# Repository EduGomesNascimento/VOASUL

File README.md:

# Site VOA-SUL

Site institucional e catálogo da **VOA-SUL**, fábrica de drones FPV e recreativos
sediada em Portão (RS).

O conteúdo foi escrito a partir do *Plano Mercadológico* e do *Plano de Marketing*
da empresa: posicionamento por qualidade (e não por preço), fabricação nacional,
controladora de voo própria, homologação ANATEL e assistência técnica local.

> **Versão preliminar.** Textos, configurações de produto, preços e dados de
> contato são genéricos e servem de estrutura. Devem ser substituídos pelos dados
> reais antes da publicação.

## Estrutura

```
index.html          Página inicial: posicionamento, diferenciais, linhas e fluxo de compra
produtos.html       Catálogo das quatro linhas (FPV 5", recreativo 250 g, peças, reparo)
homologacao.html    ANATEL x ANAC, riscos do importado sem homologação, FAQ
sobre.html          A empresa, o mercado, forma de trabalho e a marca
orcamento.html      Formulário de pedido de orçamento
contato.html        Canais de atendimento
assets/
  css/style.css     Folha de estilo única (paleta da marca em variáveis CSS)
  js/main.js        Menu mobile, validação do formulário, pré-seleção de produto
  img/              Logomarca, símbolo e favicon em SVG
```

## Como rodar localmente

Não há etapa de build nem dependências. Basta abrir `index.html` no navegador,
ou servir a pasta:

```bash
python3 -m http.server 8000
# depois acesse http://localhost:8000
```

## Publicação

O site é estático e pode ser publicado no GitHub Pages direto da branch
`main` (Settings → Pages → Deploy from a branch → `main` / `/root`), ou em
qualquer hospedagem comum, apontando o domínio `voasul.com.br` para ela.

## Pontos a completar

- [ ] Fotos reais dos drones (hoje os cartões usam um marcador com o símbolo da marca)
- [ ] Especificação técnica final e preços de cada modelo
- [ ] Endereço completo, telefone/WhatsApp e horário de atendimento
- [ ] Envio do formulário de orçamento por back-end ou serviço de formulários
      (hoje o pedido é montado e aberto no cliente de e-mail do visitante)
- [ ] Fontes das estatísticas de mercado citadas em `sobre.html`

## Convenções

- HTML estático, sem framework. Cabeçalho e rodapé são repetidos em cada página.
- Toda a paleta está em variáveis CSS no topo de `assets/css/style.css`
  (`--navy`, `--sky` etc.). Mudar a cor da marca é mudar ali.
- Textos em português do Brasil.

### Animações

As animações ficam no bloco `ANIMAÇÕES`, no fim de `assets/css/style.css`.
Os blocos entram conforme a página é rolada: o `main.js` aplica a classe
`revelar` via `IntersectionObserver` — não no HTML — para que a página
continue legível se o script não carregar. Quem tem
`prefers-reduced-motion: reduce` no sistema recebe a página sem
movimento algum, com todo o conteúdo visível.

## Projeto do drone

A pasta [`drone/`](drone/README.md) guarda o quadricóptero da VoaSul: firmware (ESP32/Pico W),
placa no KiCad (caseira de face única e versão para fábrica com Gerber), frame impresso em 3D,
plano de montagem e a luva de gestos. Ela é independente do site.

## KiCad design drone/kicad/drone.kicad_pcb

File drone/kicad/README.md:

# Placa do drone no KiCad (face única, trilhas grossas)

Projeto KiCad 7 da placa redonda (Ø97 mm) do drone. Abre no KiCad 7, 8 ou 9.

| Arquivo | O que é |
|---|---|
| `drone.kicad_pro` / `.kicad_sch` / `.kicad_pcb` | o projeto: esquema e placa |
| `drone.kicad_dru` | regras extras (sensores e resistores embaixo do ESP32 de propósito) |
| `projeto.py` | **a fonte de tudo**: peças, redes, posições, larguras e pinos do ESP32 |
| `gerar.py`, `etapas.py` | montam a placa a partir do `projeto.py` (Python do KiCad) |
| `rotear.py` | roteador próprio para face única (só numpy) |
| `gerar_esquema.py` | gera o esquema a partir do `projeto.py` |
| `modelos3d.py` + `3d/` | modelos 3D (ESP32 DevKit, MT3608, GY-BMI160, GY-BMP280 feitos aqui; o resto da biblioteca do KiCad) |
| `saidas/` | PDFs de transferência, imagens 3D, lista de redes, relatório de DRC |

## Regras da placa

- **Face única:** todo o cobre fica embaixo (B.Cu). Onde duas trilhas teriam de se cruzar
  entra um **jumper**: fio rígido por cima, do lado dos componentes (aparece como trilha fina em F.Cu
  entre duas vias, e desenhado na folha de montagem).
- **Trilhas grossas:** 2,5 mm (VBAT, drenos dos motores) · 1,5 mm (GND, 5 V, 3V3) · 1,2 mm (sinais).
  Só afinam para 0,8 mm nos últimos 3 mm antes de um pino de passo 2,54.
- **Folga de 0,8 mm** entre cobres de redes diferentes, inclusive entre ilhas de pinos (ilhas
  ovais de 1,7 × 3,0 mm), para o toner amassado não encostar.
- **Anel de VBAT** de 2,5 mm por dentro da borda, e **plano de GND** no resto.
- Peças SMD (MOSFET SOT-23, diodo SS34, capacitor 0805) ficam **embaixo, no lado do cobre**,
  fora dos raios do frame (que passam a 2 mm da placa nas diagonais).
- **BMI160 e BMP280 ficam embaixo do ESP32**, entre as barras fêmea (8,5 mm de vão), soldados
  direto com barra macho. O giroscópio fica perto do centro do drone.

## Pinos do ESP32 (mudaram!)

Para não cruzar trilha, os pinos seguem a ordem física dos braços. O `include/board_esp32.h`
já está atualizado:

| Função | GPIO | | Função | GPIO |
|---|---|---|---|---|
| Motor FR | 17 | | Sonar baixo TRIG / ECHO | 14 / 27 |
| Motor RR | 4 | | Sonar frente TRIG / ECHO | 13 / 12 |
| Motor RL | 23 | | IR esquerdo / direito | 36 / 39 |
| Motor FL | 19 | | Bateria (ADC1) | 35 |
| I²C 1 (BMP280) SDA / SCL | 21 / 22 | | LED | 2 |
| I²C 2 (BMI160) SDA / SCL | 16 / 18 | | Fluxo óptico MISO / SCK / MOSI / CS | 32 / 33 / 25 / 26 |

## Fluxo óptico (J4): opcional

O **J4** é o conector do sensor de fluxo óptico **PMW3901** (SPI). A placa e o firmware
funcionam **com e sem** o módulo:

- sem o módulo, o J4 fica vazio e o drone voa como sempre;
- com o módulo, o firmware o encontra sozinho no boot (lê o ID do chip) e passa a frear a
  deriva quando o manche está solto. A página do celular mostra o estado no quadro **Fluxo**;
- se o módulo parar de responder em voo (fio solto), o firmware percebe em menos de 1 s e
  segue sem ele.

O J4 é uma barra **2×3** logo abaixo do ESP32. Visto de cima: fileira de cima **MISO, SCK, MOSI**;
fileira de baixo **3V3, GND, CS** (o quadrado verde da folha de montagem é o 3V3).
O módulo vai embaixo do drone, com a lente para baixo. Ligue e desligue só com o drone
**desligado**. Teste e ajuste: `docs/PLANO_DE_MONTAGEM.md`, fase 12.

## Arquivos para usar já

| Para | Arquivo |
|---|---|
| Transferência térmica (imprimir 1:1, laser) | `saidas/transferencia_B_Cu.pdf` |
| Montagem por cima / por baixo | `saidas/montagem_cima.pdf`, `saidas/montagem_baixo_vista_por_baixo.pdf` |
| Lista de jumpers | `saidas/jumpers.txt` (11: 6 de GND, 1 de 3V3, 4 de sinal de motor) |
| Teste de continuidade | `saidas/redes.txt` |
| Esquema | `saidas/esquema.pdf` |
| Mandar fazer na fábrica | `pro/drone_pro_gerber.zip` (+ `pro/drone_pro.kicad_pcb`) |
| Ver em 3D | `saidas/drone3d_*.png`; interativo: `python3 -m http.server` nesta pasta e abrir `saidas/visualizador3d.html` |

## Regerar tudo

Tudo de uma vez: `./gerar_tudo.sh` (leva uns 30–40 minutos por causa do roteador). Passo a passo:

```bash
python3 gerar.py placa        # peças e redes (Python do KiCad: /usr/bin/python3)
python3 gerar.py exportar     # geometria.json para o roteador
python3 rotear.py geometria.json rotas.json   # qualquer Python com numpy
python3 gerar.py aplicar      # trilhas, jumpers, plano de GND
python3 gerar.py drc          # verificação de regras -> drc.txt
python3 gerar_esquema.py      # esquema
python3 gerar.py saidas       # PDFs de transferência e 3D
```

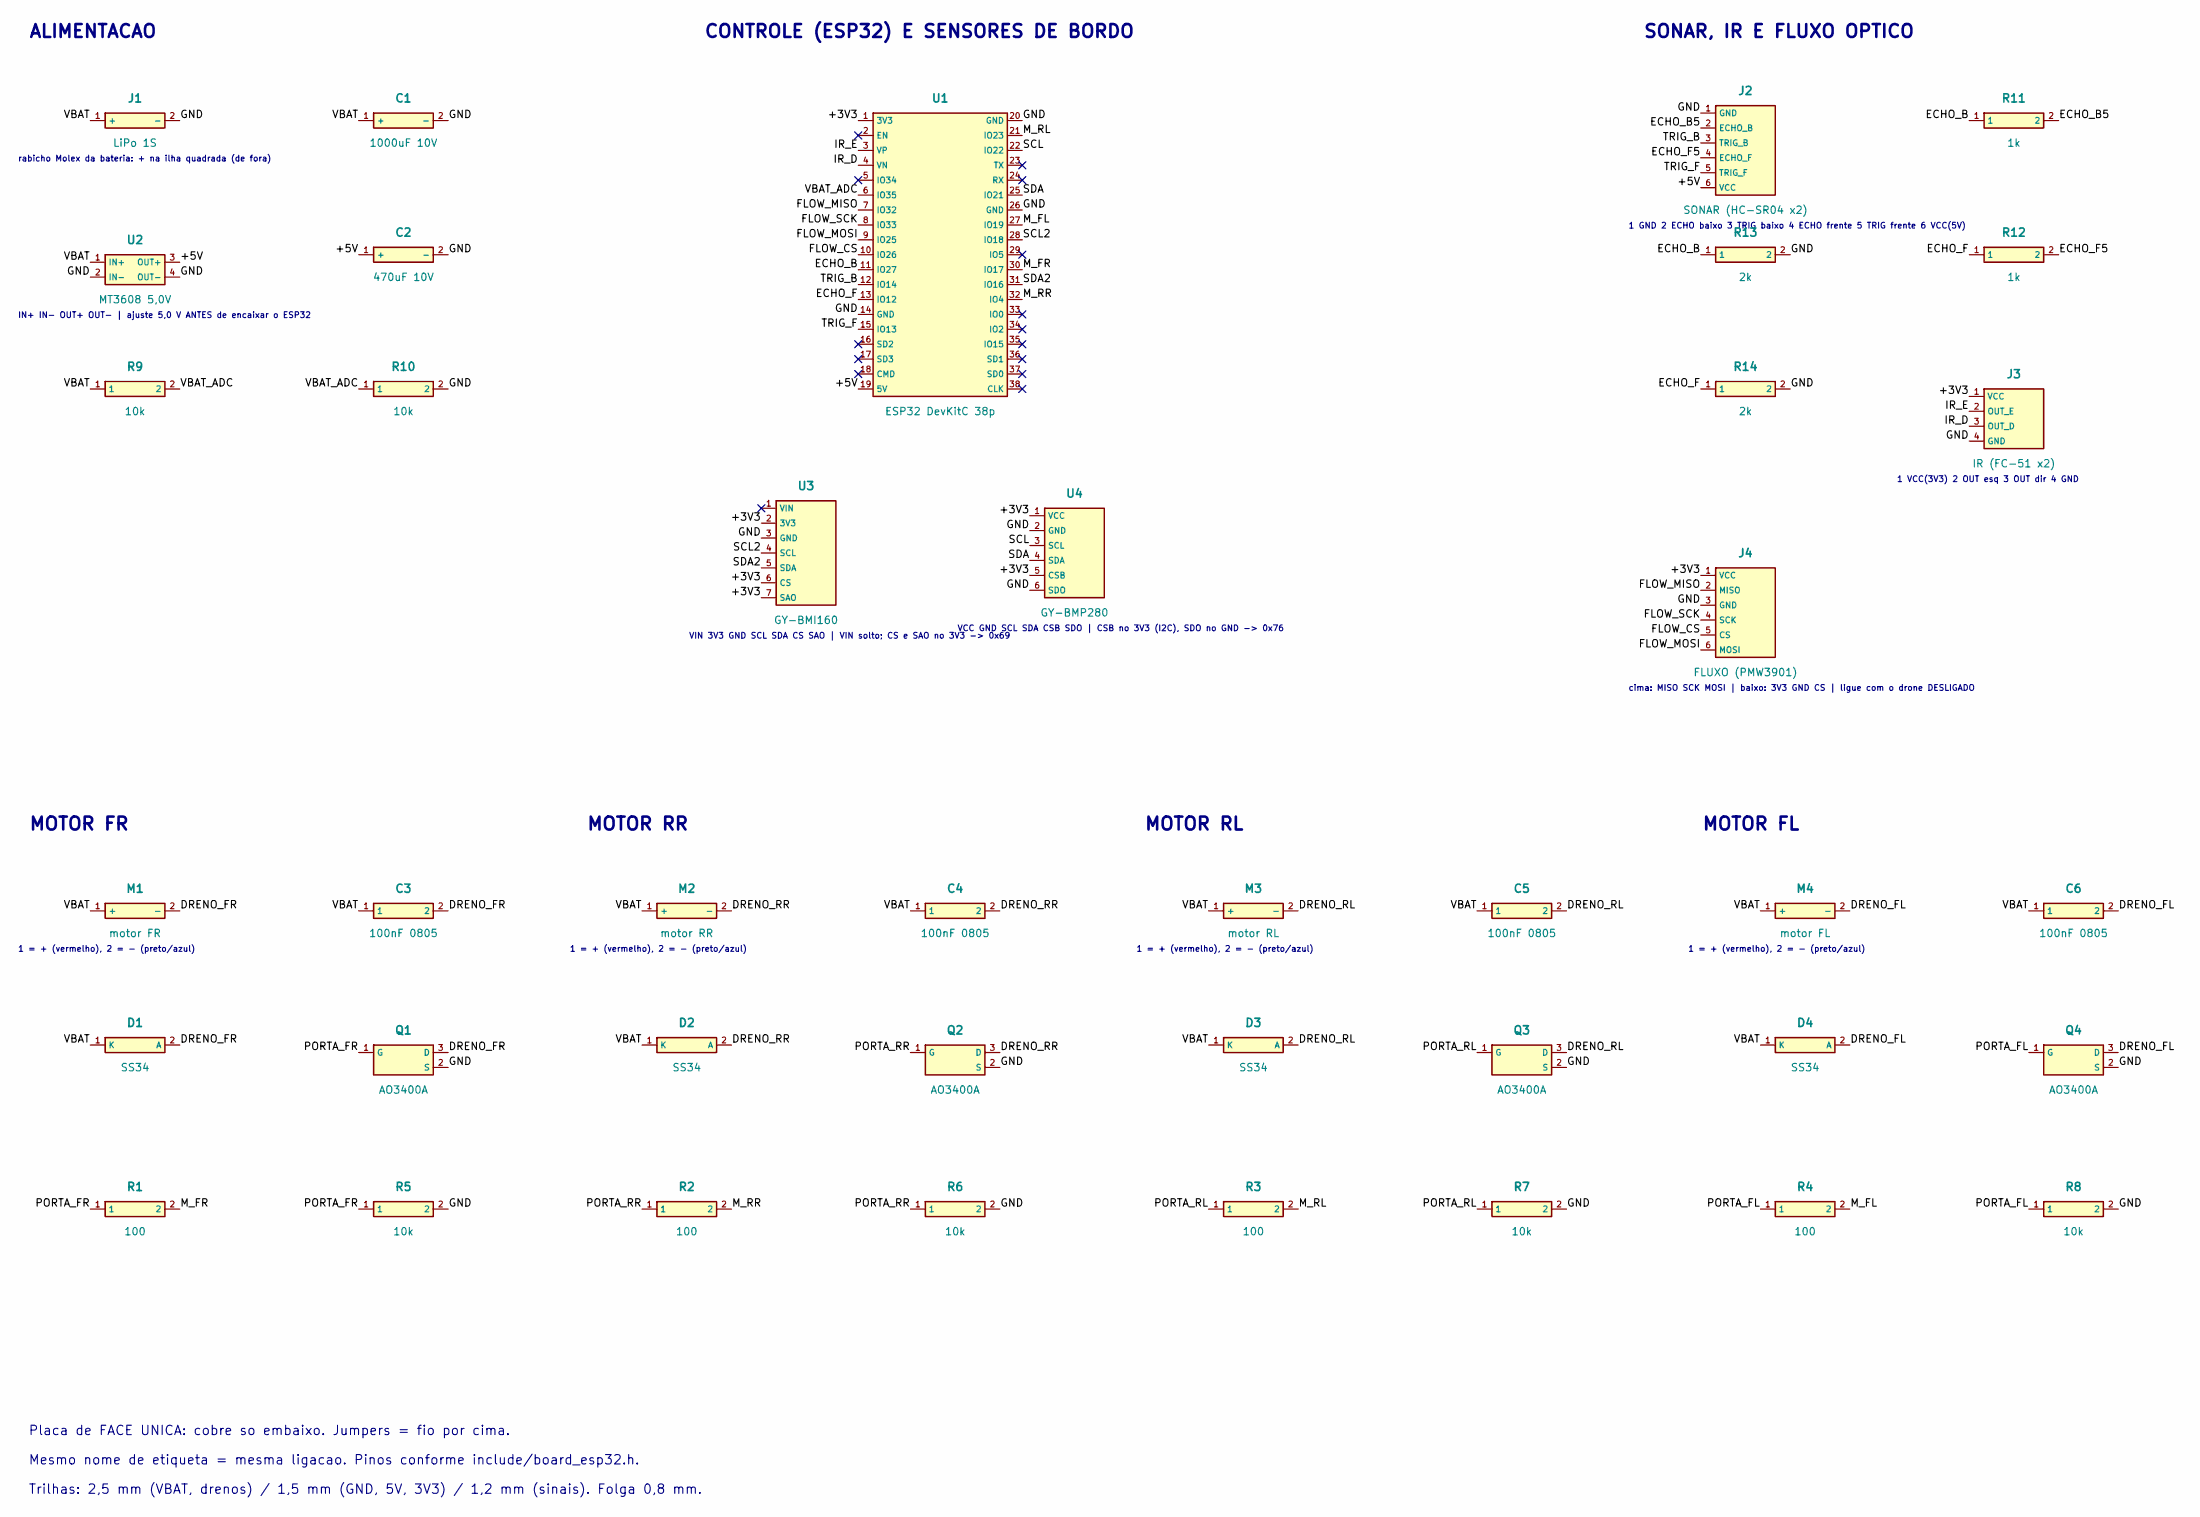
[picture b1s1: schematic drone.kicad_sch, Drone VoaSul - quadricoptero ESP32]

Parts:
C1: 1000uF 10V; CP_Radial_D8.0mm_P3.50mm
C2: 470uF 10V; CP_Radial_D6.3mm_P2.50mm
C3, C4, C5, C6: 100nF 0805; C_0805_2012Metric
D1, D2, D3, D4: SS34; D_SMA
J1: LiPo 1S; Ilhas_bateria
J2: SONAR (HC-SR04 x2); PinHeader_1x06_P2.54mm_Vertical
J3: IR (FC-51 x2); PinHeader_1x04_P2.54mm_Vertical
J4: FLUXO (PMW3901); PinHeader_2x03_P2.54mm_Vertical
M1: motor FR; Ilhas_motor
M2: motor RR; Ilhas_motor
M3: motor RL; Ilhas_motor
M4: motor FL; Ilhas_motor
Q1, Q2, Q3, Q4: AO3400A; SOT-23
R1, R2, R3, R4: 100; R_Axial_DIN0204_L3.6mm_D1.6mm_P2.54mm_Vertical
R5, R6, R7, R8, R9, R10: 10k; R_Axial_DIN0204_L3.6mm_D1.6mm_P2.54mm_Vertical
R11, R12: 1k; R_Axial_DIN0204_L3.6mm_D1.6mm_P2.54mm_Vertical
R13, R14: 2k; R_Axial_DIN0204_L3.6mm_D1.6mm_P2.54mm_Vertical
U1: ESP32 DevKitC 38p; ESP32_DevKitC_38p
U2: MT3608 5,0V; MT3608_modulo
U3: GY-BMI160; GY_BMI160
U4: GY-BMP280; GY_BMP280

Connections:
+3V3: J3.1 (VCC), J4.1 (VCC), U1.1 (3V3), U3.2 (3V3), U3.6 (CS), U3.7 (SAO), U4.1 (VCC), U4.5 (CSB)
+5V: C2.1 (+), J2.6 (VCC), U1.19 (5V), U2.3 (OUT+)
DRENO_FL: C6.2, D4.2 (A), M4.2 (-), Q4.3 (D)
DRENO_FR: C3.2, D1.2 (A), M1.2 (-), Q1.3 (D)
DRENO_RL: C5.2, D3.2 (A), M3.2 (-), Q3.3 (D)
DRENO_RR: C4.2, D2.2 (A), M2.2 (-), Q2.3 (D)
ECHO_B: R11.1, R13.1, U1.11 (IO27)
ECHO_B5: J2.2 (ECHO_B), R11.2
ECHO_F: R12.1, R14.1, U1.13 (IO12)
ECHO_F5: J2.4 (ECHO_F), R12.2
FLOW_CS: J4.5 (CS), U1.10 (IO26)
FLOW_MISO: J4.2 (MISO), U1.7 (IO32)
FLOW_MOSI: J4.6 (MOSI), U1.9 (IO25)
FLOW_SCK: J4.4 (SCK), U1.8 (IO33)
GND: C1.2 (-), C2.2 (-), J1.2 (-), J2.1 (GND), J3.4 (GND), J4.3 (GND), Q1.2 (S), Q2.2 (S), Q3.2 (S), Q4.2 (S), R5.2, R6.2, R7.2, R8.2, R10.2, R13.2, R14.2, U1.14 (GND), U1.20 (GND), U1.26 (GND), U2.2 (IN-), U2.4 (OUT-), U3.3 (GND), U4.2 (GND), U4.6 (SDO)
IR_D: J3.3 (OUT_D), U1.4 (VN)
IR_E: J3.2 (OUT_E), U1.3 (VP)
M_FL: R4.2, U1.27 (IO19)
M_FR: R1.2, U1.30 (IO17)
M_RL: R3.2, U1.21 (IO23)
M_RR: R2.2, U1.32 (IO4)
PORTA_FL: Q4.1 (G), R4.1, R8.1
PORTA_FR: Q1.1 (G), R1.1, R5.1
PORTA_RL: Q3.1 (G), R3.1, R7.1
PORTA_RR: Q2.1 (G), R2.1, R6.1
SCL: U1.22 (IO22), U4.3 (SCL)
SCL2: U1.28 (IO18), U3.4 (SCL)
SDA: U1.25 (IO21), U4.4 (SDA)
SDA2: U1.31 (IO16), U3.5 (SDA)
TRIG_B: J2.3 (TRIG_B), U1.12 (IO14)
TRIG_F: J2.5 (TRIG_F), U1.15 (IO13)
VBAT: C1.1 (+), C3.1, C4.1, C5.1, C6.1, D1.1 (K), D2.1 (K), D3.1 (K), D4.1 (K), J1.1 (+), M1.1 (+), M2.1 (+), M3.1 (+), M4.1 (+), R9.1, U2.1 (IN+)
VBAT_ADC: R9.2, R10.1, U1.6 (IO35)

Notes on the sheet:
ALIMENTACAO
rabicho Molex da bateria: + na ilha quadrada (de fora)
IN+ IN- OUT+ OUT- | ajuste 5,0 V ANTES de encaixar o ESP32
CONTROLE (ESP32) E SENSORES DE BORDO
VIN 3V3 GND SCL SDA CS SAO | VIN solto; CS e SAO no 3V3 -> 0x69
VCC GND SCL SDA CSB SDO | CSB no 3V3 (I2C), SDO no GND -> 0x76
SONAR, IR E FLUXO OPTICO
1 GND 2 ECHO baixo 3 TRIG baixo 4 ECHO frente 5 TRIG frente 6 VCC(5V)
1 VCC(3V3) 2 OUT esq 3 OUT dir 4 GND
cima: MISO SCK MOSI | baixo: 3V3 GND CS | ligue com o drone DESLIGADO
MOTOR FR
1 = + (vermelho), 2 = - (preto/azul)
MOTOR RR
MOTOR RL
MOTOR FL
Placa de FACE UNICA: cobre so embaixo. Jumpers = fio por cima.
Mesmo nome de etiqueta = mesma ligacao. Pinos conforme include/board_esp32.h.
Trilhas: 2,5 mm (VBAT, drenos) / 1,5 mm (GND, 5V, 3V3) / 1,2 mm (sinais). Folga 0,8 mm.

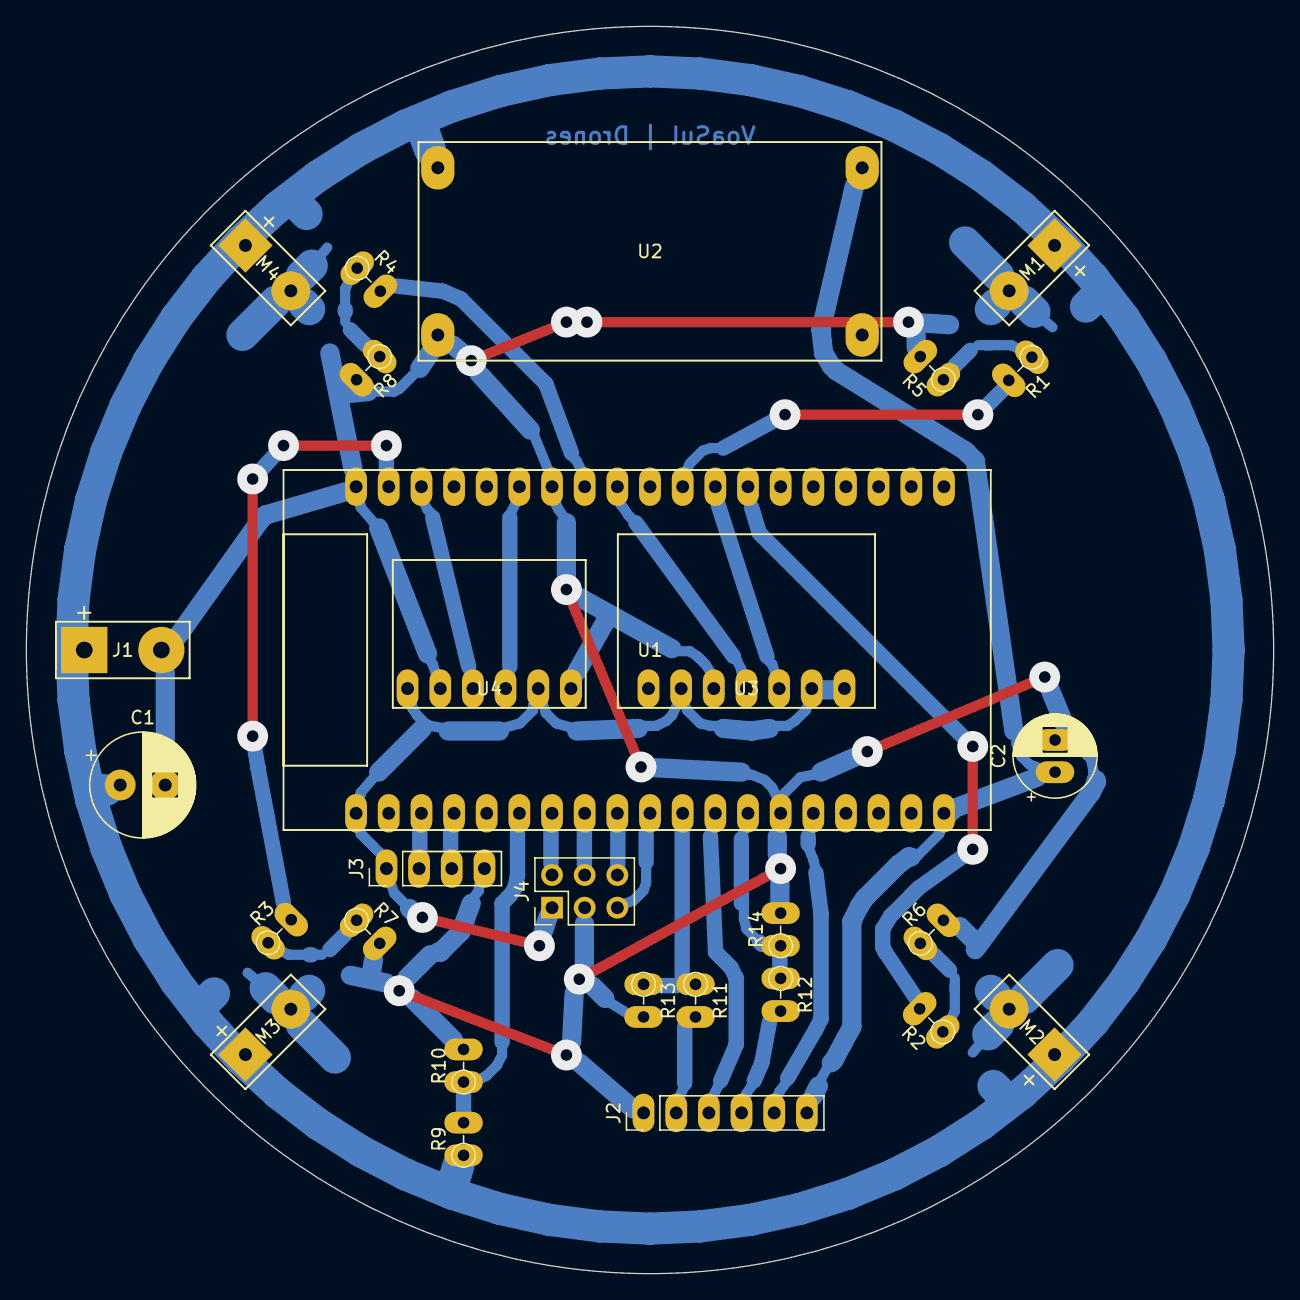
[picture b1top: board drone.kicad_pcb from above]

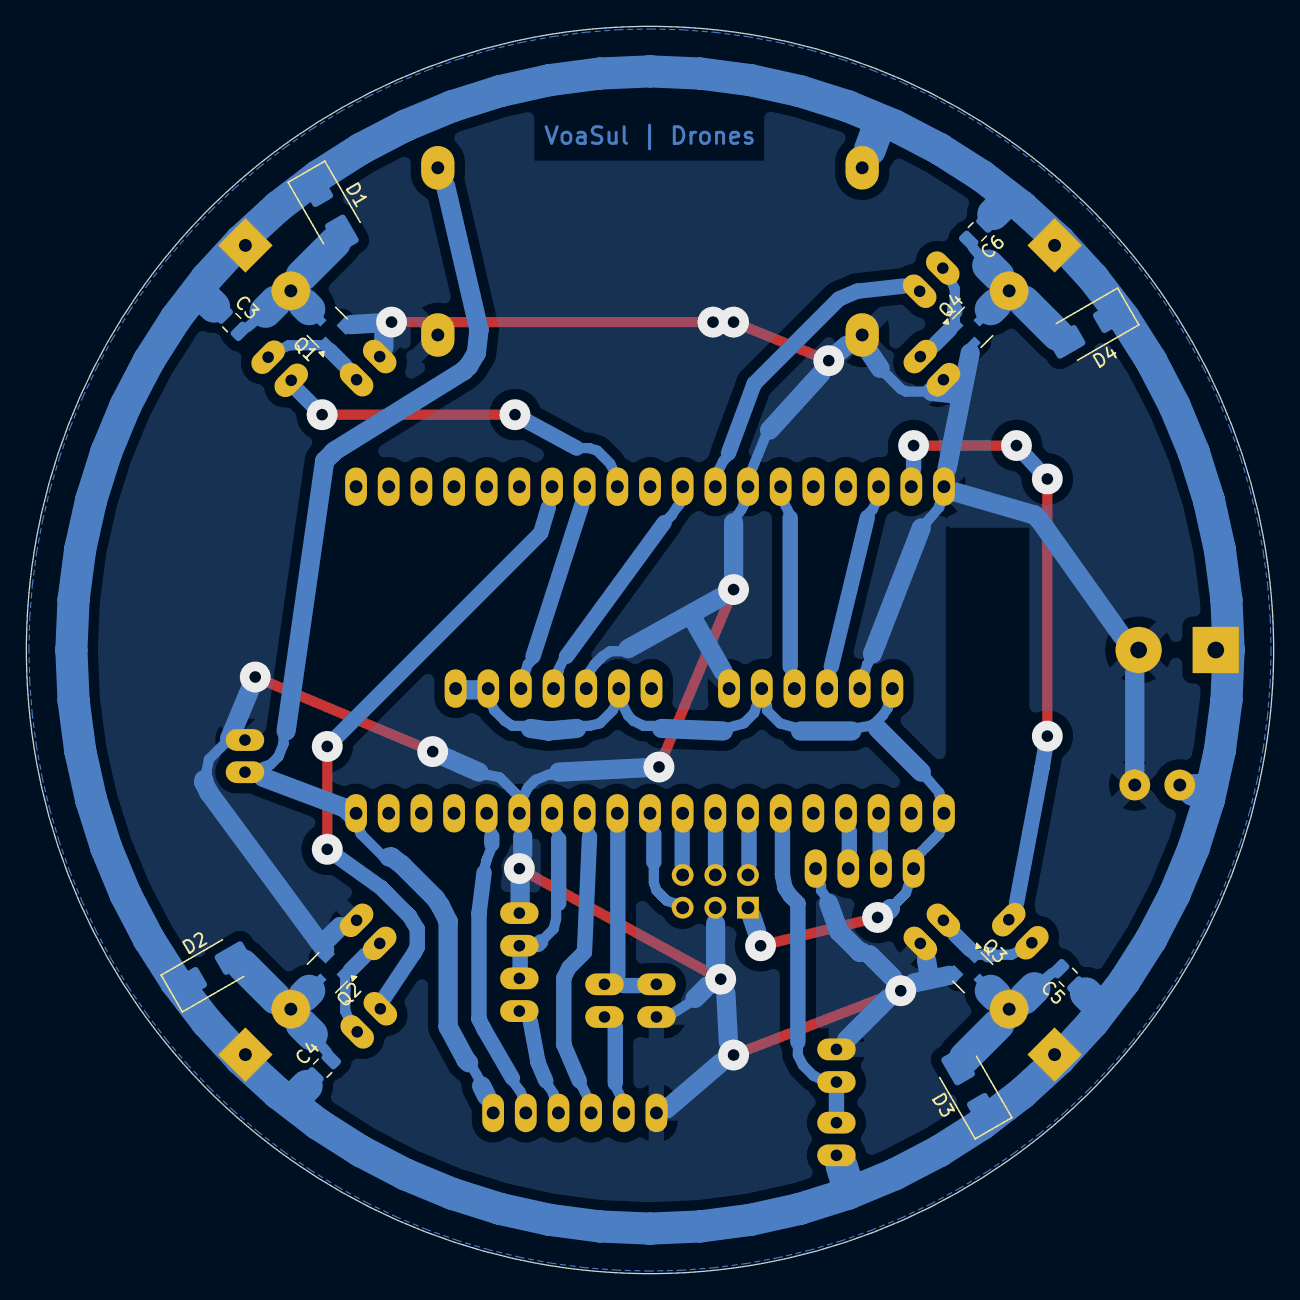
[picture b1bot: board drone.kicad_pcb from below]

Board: 2 copper layers, 97.0 x 97.0 mm, 40 parts (12 on the bottom side), 33 nets.

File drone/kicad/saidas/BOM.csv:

Qtd,Referencias,Valor,Descricao,Pegada,Montagem,Lado,LCSC,Observacao
1,C1,1000uF 10V,"Capacitor eletrolitico 1000 uF 10-16 V, D8 mm, passo 3,5 mm",CP_Radial_D8.0mm_P3.50mm,THT,cima,,polaridade
1,C2,470uF 10V,"Capacitor eletrolitico 470 uF 10-16 V, D6,3 mm, passo 2,5 mm",CP_Radial_D6.3mm_P2.50mm,THT,cima,,polaridade
4,C3 C4 C5 C6,100nF 0805,"Capacitor ceramico 100 nF 50 V X7R, 0805",C_0805_2012Metric,SMD,baixo,C49678,face de baixo
4,D1 D2 D3 D4,SS34,"Diodo Schottky SS34 40 V 3 A, SMA",D_SMA,SMD,baixo,C8678,"face de baixo, faixa para fora"
1,J1,LiPo 1S,Rabicho Molex 51005 macho com fio 24 AWG,Ilhas_bateria,THT,cima,,+ (vermelho) na ilha quadrada
1,J2,SONAR (HC-SR04 x2),"Barra de pinos macho 1x6, 2,54 mm",PinHeader_1x06_P2.54mm_Vertical,THT,cima,,conector dos sonares
1,J3,IR (FC-51 x2),"Barra de pinos macho 1x4, 2,54 mm",PinHeader_1x04_P2.54mm_Vertical,THT,cima,,conector dos IR
1,J4,FLUXO (PMW3901),"Barra de pinos macho 2x3, 2,54 mm",PinHeader_2x03_P2.54mm_Vertical,THT,cima,,fluxo optico (opcional); ou 2 pedacos de 1x3
1,M1,motor FR,Ilhas para o motor coreless 1020,Ilhas_motor,THT,cima,,fios do motor; + na ilha quadrada
1,M2,motor RR,Ilhas para o motor coreless 1020,Ilhas_motor,THT,cima,,fios do motor; + na ilha quadrada
1,M3,motor RL,Ilhas para o motor coreless 1020,Ilhas_motor,THT,cima,,fios do motor; + na ilha quadrada
1,M4,motor FL,Ilhas para o motor coreless 1020,Ilhas_motor,THT,cima,,fios do motor; + na ilha quadrada
4,Q1 Q2 Q3 Q4,AO3400A,"MOSFET canal N AO3400A 30 V 5,7 A, SOT-23",SOT-23,SMD,baixo,C20917,face de baixo
4,R1 R2 R3 R4,100,Resistor 100 ohm 1/4 W,R_Axial_DIN0204_L3.6mm_D1.6mm_P2.54mm_Vertical,THT,cima,,em pe; 100-220 ohm servem
6,R5 R6 R7 R8 R9 R10,10k,Resistor 10 kohm 1/4 W,R_Axial_DIN0204_L3.6mm_D1.6mm_P2.54mm_Vertical,THT,cima,,em pe
2,R11 R12,1k,Resistor 1 kohm 1/4 W,R_Axial_DIN0204_L3.6mm_D1.6mm_P2.54mm_Vertical,THT,cima,,em pe
2,R13 R14,2k,Resistor 2 kohm 1/4 W,R_Axial_DIN0204_L3.6mm_D1.6mm_P2.54mm_Vertical,THT,cima,,em pe; 1k8 ou 2k2 servem
1,U1,ESP32 DevKitC 38p,"Placa ESP32 DevKitC V4, 38 pinos, WROOM-32",ESP32_DevKitC_38p,THT,cima,,em 2 barras femea 1x19
1,U2,"MT3608 5,0V",Modulo step-up MT3608,MT3608_modulo,THT,cima,,"em 4 pernas de fio; ajuste 5,0 V antes do ESP32"
1,U3,GY-BMI160,Modulo giroscopio/acelerometro GY-BMI160,GY_BMI160,THT,cima,,"barra macho baixa, embaixo do ESP32"
1,U4,GY-BMP280,Modulo barometro GY-BMP280-3.3 (6 pinos),GY_BMP280,THT,cima,,"barra macho baixa, embaixo do ESP32"
2,U1 (ESP32),,"Barra de pinos femea 1x19, 2,54 mm",,fora da placa,,,corte de 2 barras 1x40
4,M1-M4,,Motor coreless 1020 (2 CW + 2 CCW),,fora da placa,,,ja comprado
1,J1,,Bateria LiPo 1S 500-600 mAh 25C+ com Molex 51005,,fora da placa,,,ex.: Leao LB530LP1

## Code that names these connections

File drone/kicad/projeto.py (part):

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    'PIN_SONAR_DOWN_TRIG': 14, 'PIN_SONAR_DOWN_ECHO': 27,
    'PIN_SONAR_FRONT_TRIG': 13, 'PIN_SONAR_FRONT_ECHO': 12,
    'PIN_IR_LEFT': 36, 'PIN_IR_RIGHT': 39, 'PIN_VBAT': 35, 'PIN_STATUS_LED': 2,
    'PIN_FLOW_MISO': 32, 'PIN_FLOW_SCK': 33, 'PIN_FLOW_MOSI': 25, 'PIN_FLOW_CS': 26,
}


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# de cima (visto de cima), da esquerda p/ a direita: J3 (IR) | divisor da bateria |
# J4 (fluxo optico) | sonar (resistores + J2)
peca('J3', 'IR (FC-51 x2)', 'CONN4', -20.5, -17.0, rot=90,
     pinos={'1': '+3V3', '2': 'IR_E', '3': 'IR_D', '4': 'GND'},
     nota='1 VCC(3V3) 2 OUT esq 3 OUT dir 4 GND')
# divisor da bateria (IO34): 10k/10k, em pe
# (encostado no anel de VBAT: so o sinal fino VBAT_ADC atravessa a placa)
peca('R9', '10k', 'R_PE', -14.5, -39.3, rot=90, pinos={'1': 'VBAT', '2': 'VBAT_ADC'})
peca('R10', '10k', 'R_PE', -14.5, -33.6, rot=90, pinos={'1': 'VBAT_ADC', '2': 'GND'})
# fluxo optico PMW3901: OPCIONAL. Sem o modulo o drone voa igual; o firmware
# descobre sozinho no boot se ele esta ligado (le o ID do chip).
# Barra 2x3 logo abaixo dos pinos 32/33/25/26 do ESP32: as trilhas ficam curtinhas
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#   fileira de cima : MISO SCK MOSI   (pinos 2 4 6)
#   fileira de baixo: 3V3  GND CS     (pinos 1 3 5)
peca('J4', 'FLUXO (PMW3901)', 'CONN2x3', -7.62, -20.04, rot=90,
     pinos={'1': '+3V3', '2': 'FLOW_MISO', '3': 'GND', '4': 'FLOW_SCK', '5': 'FLOW_CS', '6': 'FLOW_MOSI'},
     nota='cima: MISO SCK MOSI | baixo: 3V3 GND CS | ligue com o drone DESLIGADO')

# sonar. Divisores do ECHO (5 V -> 3,3 V): 1k em serie, 2k para o GND, em pe.
#  - ECHO baixo: R13 (2k) e R11 (1k) lado a lado, abaixo do J4.
#  - ECHO frente: R14 (2k) e R12 (1k) em coluna, abaixo do GND do ESP32 (pino 14).
peca('R13', '2k', 'R_PE', -0.5, -26.0, rot=-90, pinos={'1': 'ECHO_B', '2': 'GND'})
peca('R11', '1k', 'R_PE', 3.54, -26.0, rot=-90, pinos={'1': 'ECHO_B', '2': 'ECHO_B5'})
peca('R14', '2k', 'R_PE', 10.16, -23.0, rot=90, pinos={'1': 'ECHO_F', '2': 'GND'})
peca('R12', '1k', 'R_PE', 10.16, -25.54, rot=-90, pinos={'1': 'ECHO_F', '2': 'ECHO_F5'})
# ordem dos pinos = ordem das trilhas que chegam (nada cruza)
peca('J2', 'SONAR (HC-SR04 x2)', 'CONN6', -0.5, -36.0, rot=90,
     pinos={'1': 'GND', '2': 'ECHO_B5', '3': 'TRIG_B', '4': 'ECHO_F5', '5': 'TRIG_F', '6': '+5V'},
     nota='1 GND 2 ECHO baixo 3 TRIG baixo 4 ECHO frente 5 TRIG frente 6 VCC(5V)')

# ---- jumpers fixos (fio por cima), posicionados a mao: o roteador nao acha sozinho
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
